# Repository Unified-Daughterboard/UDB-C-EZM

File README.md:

# Unified Daughterboard C Series - EZM variant

## Introduction
The Unified Daughterboard Project is an open standard to unify the USB daughterboards used in custom mechanical keyboard projects.  
The Unified Daughterboard allows designers to easily implementing electrical protection via a tested proven PCB, and allows users to maintain and repair their keyboards in the future.  
  
For more details on the Unified Daughterboard project, see the [main website](https://unified-daughterboard.github.io/).

## C Series

The C5 daughterboard is the current most recent revision to the classic square form-factor daughterboard, with its roots in the C1 which was designed to be compatible with Wilba's keyboards.
The daughterboard features the following:

- ESD protection, overcurrent protection, overvoltage protection, shielding noise decoupling, and single-path grounding to chassis functionality
- Two variants: The new Molex Pico-EZmate and the classic JST-SH
- 1:1 connector pinout to retain compatibility with existing PCBs
- Same form factor as the older C3 series, allowing for daughterboard upgrades
  
**This is the EZM variant using the Pico-EZMate connector.**  
For background on why two variants exist, please see the [announcement post](https://unified-daughterboard.github.io/#/announcements/announcement-20231022).

The C5 version of the daughterboard was split into two versions: C-JSH and C-PEM, repectively pertaining to versions using the JST-SH connector and the MOLEX EZMate connector.

## Using the C series uDB in your design
Please [visit the docs](https://unified-daughterboard.github.io/) for detailed implementation references and notices.  

## Previews

## Credits
- [Gondolindrim](https://github.com/Gondolindrim)
- [hineybush](https://hineybush.com/)
- [ai03](https://ai03.com/)
- [GEON](https://geon.works/)
- [Sleepdealer](https://sleepdealer.xyz)
- [Xelus](https://xelus.me)
- [James (AKB)](https://alchemistkeyboards.com/)
- [kkatano](https://github.com/kkatano)
- [ToastyStoemp](https://vwolf.be)
- [Upas](https://cannonkeys.com)

C3 Unified:
- [Wilba](https://wilba.tech)
- Xondat
- [aeryxz](https://github.com/aeryxz)
- [Maximillian](https://github.com/Maximillian)

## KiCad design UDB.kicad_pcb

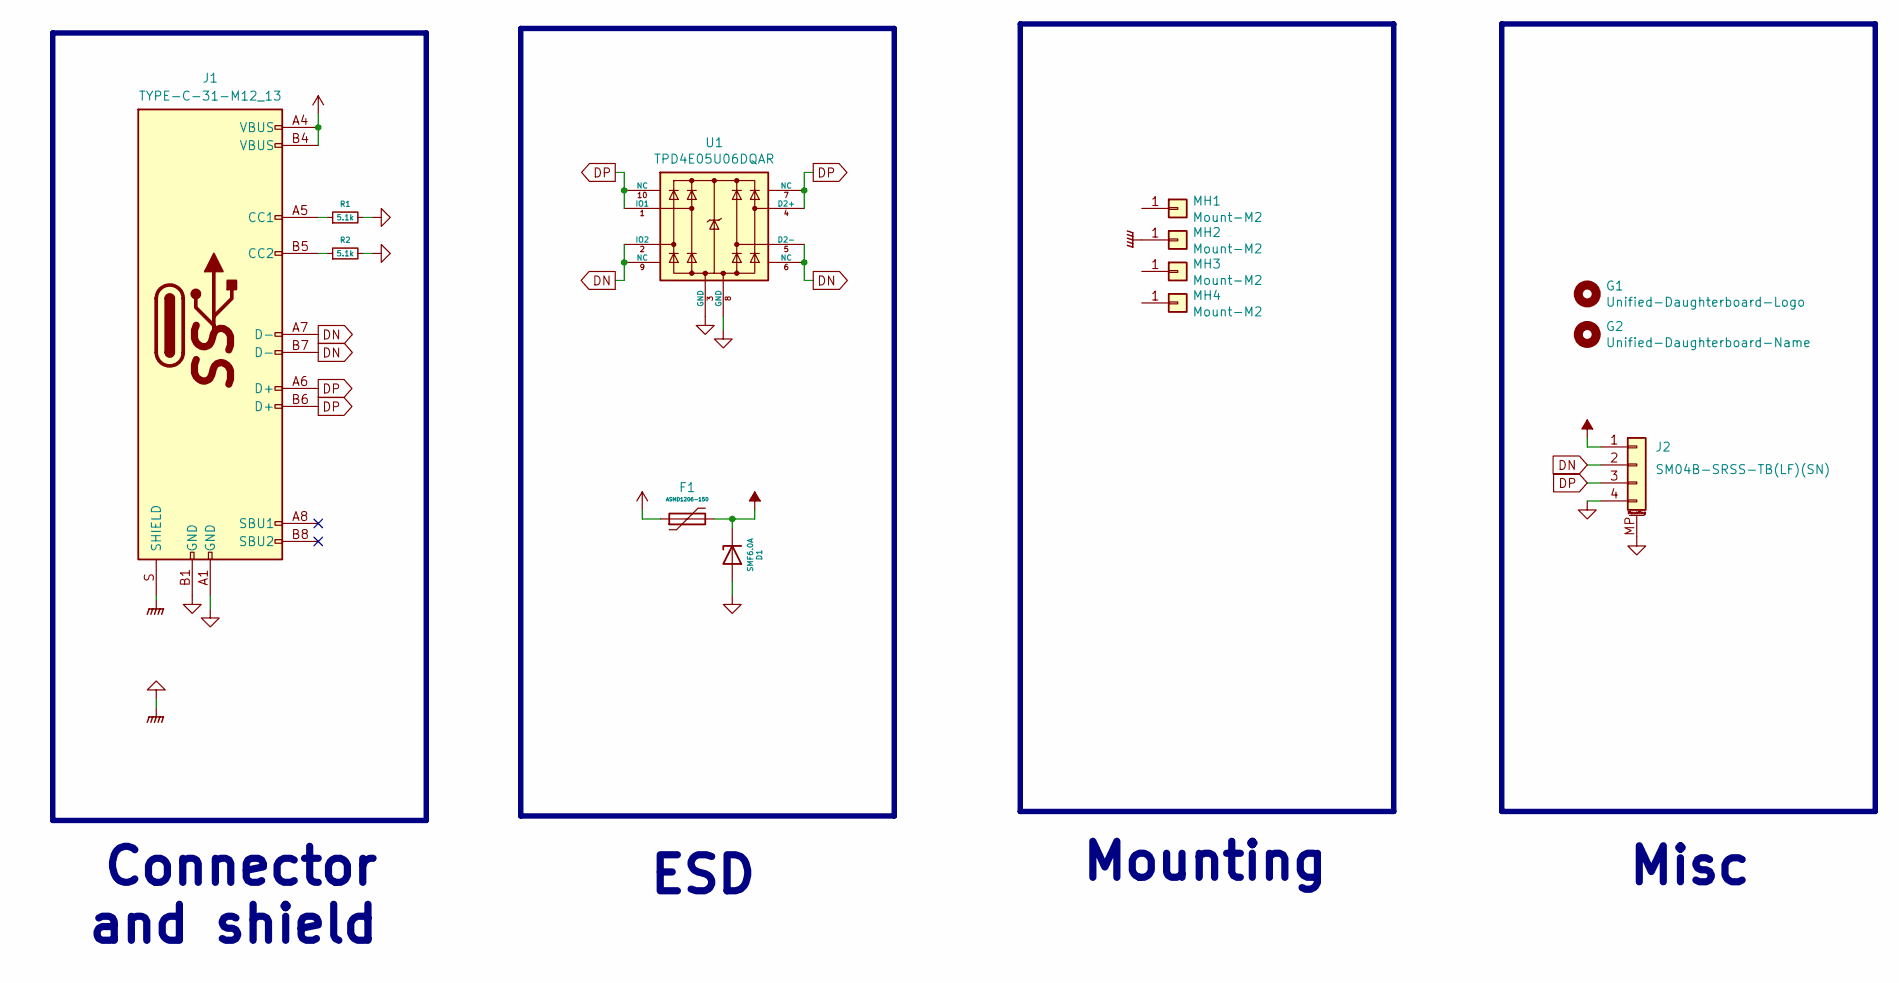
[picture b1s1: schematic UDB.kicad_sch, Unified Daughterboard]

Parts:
D1: SMF6.0A; D_SOD-123; Manufacturer Part Number SMF6.0A; LCSC Part Number C708002
F1: ASMD1206-150; Fuse_1206_3216Metric; Manufacturer Part Number ASMD1206-150; LCSC Part Number C135342
G1: Unified-Daughterboard-Logo; Unified-Daughterboard-Logo.pretty
G2: Unified-Daughterboard-Name; Unified-Daughterboard-Name.pretty
J1: TYPE-C-31-M12_13; TYPE-C-31-M-12; Manufacturer Part Number TYPE-C-31-M-12; LCSC Part Number C165948
J2: SM04B-SRSS-TB(LF)(SN); SM04B-SRSS-TB(LF)(SN)_mounting-reliefs; Manufacturer Part Number SM04B-SRSS-TB(LF)(SN); LCSC Part Number C160404
MH1, MH2, MH3, MH4: Mount-M2; Generic-Mounthole
R1: 5.1k; R_0402_1005Metric; Manufacturer Part Number 0402WGF5101TCE; LCSC Part Number C25905
R2: 5.1k; R_0402_1005Metric
U1: TPD4E05U06DQAR; USON-10_2.5x1.0mm_P0.5mm; Manufacturer Part Number TPD4E05U06DQAR; LCSC Part Number C138714

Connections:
DN: J1.A7 (D-), J1.B7 (D-), J2.2, U1.2 (IO2), U1.5 (D2-), U1.6 (NC), U1.9 (NC)
DP: J1.A6 (D+), J1.B6 (D+), J2.3, U1.1 (IO1), U1.4 (D2+), U1.7 (NC), U1.10 (NC)
GND: D1.2 (A), J1.A1 (GND), J1.B1 (GND), J1.S (SHIELD), J2.4, J2.MP (MountPin), MH2.1, R1.2, R2.2, U1.3 (GND), U1.8 (GND)
unnamed: J1.A5 (CC1), R1.1
unnamed: J1.B5 (CC2), R2.1
VBUS: F1.1, J1.A4 (VBUS), J1.B4 (VBUS)
VCOM: D1.1 (K), F1.2, J2.1

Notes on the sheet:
Connector and shield
Misc
Mounting
ESD

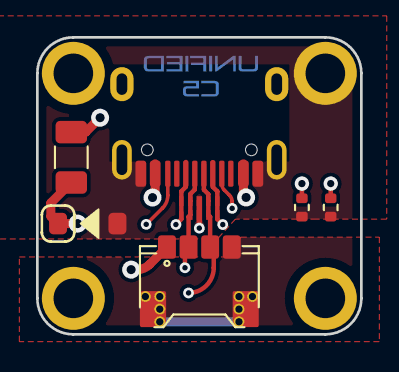
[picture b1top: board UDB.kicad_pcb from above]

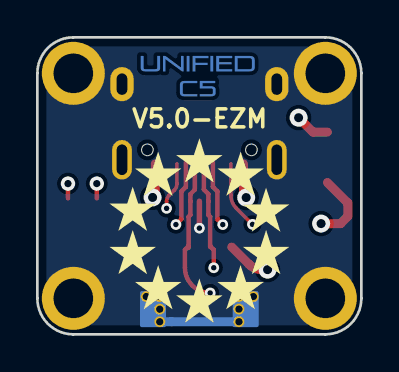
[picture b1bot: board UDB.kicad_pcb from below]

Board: 4 copper layers, 18.0 x 16.5 mm, 13 parts (2 on the bottom side), 7 nets.

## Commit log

2022-10-14 Major redesign, almost complete routing, new logo
2022-10-14 Skew phase adjustment for outer USB diff pair
2022-11-01 Update gitignore to include relese folder with final manufacturing files
2022-11-01 Edit component metadata, final checks, release
2022-12-15 Swap footprint
2023-01-17 Add prod files and 3D model
2023-01-17 Fix missing uson chip in 3D model; add implementation example
2023-01-17 Add images
2023-01-17 Create LICENSE
2023-01-17 Add readme
2023-01-17 Fix typo
2023-02-24 Retune trace thickness and USB data phase skew; plate connector mounting points to GND signal
2023-03-29 Add 4.1 silkscreen indicators to PCB
2023-04-11 Update fuse part number in production BOM
2023-06-04 fix BOM file and use correct manufacturer part num for fuse
2023-08-19 New version files and pertaining prod files added
2023-08-19 Rename prod files, rewrite README
2023-08-19 New C5 version files, remove old prod files
2023-08-19 Redo README
2023-10-22 Update logo to C5
2023-10-22 Update production files
2023-10-22 Add `5.0-JSH` silkscreen marking
2023-10-22 Add C5 logo and -EZM marking; update prod files
